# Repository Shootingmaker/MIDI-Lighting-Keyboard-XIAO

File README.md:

# MIDI-Lighting-Keyboard-XIAO  

This repository for like this video.  
  
1.[Board setting]  
File ->>> Enviroment ->>> add URL  
https://files.seeedstudio.com/arduino/package_seeeduino_boards_index.json  
 
 [Tool ->>> Setting]   
Board : Seed Studio XIAO  
USB stack : Arduino  
Debug:off  
 
2.[Library Install]  
FastLED 3.3.3 "5kft" fork.  
Tools -> Library manager.  
https://github.com/5kft/FastLED/tree/platform-xiao  
 
Arduiono MIDI 5.0  
Tools -> Library manager.  
https://github.com/FortySevenEffects/arduino_midi_library  
 
Arduino USB-MIDI  
Tools -> Library manager.  
https://github.com/lathoub/Arduino-USBMIDI  
 
MIDIUSB  
Tools -> Library manager.  
https://github.com/arduino-libraries/MIDIUSB  
 
3.[Over write "buffer memory" & "RunningStatus" setting.]  
 
 "midi_Settings.h" over write or  USE static  const  
 -> static const unsigned SysExMaxSize = 10240;  // more is better.  
 -> static const bool UseRunningStatus = true;  

4.[HARDWARE Wireing to LED (SK9822 or APA102)]  

 5V    with Capacitor 100uF is Better.  
 SDI(Serial DATA In = MOSI) is  Pin:10(XIAO)  
 CKI(Clock In)  is  Pin:8(XIAO)  
 GND

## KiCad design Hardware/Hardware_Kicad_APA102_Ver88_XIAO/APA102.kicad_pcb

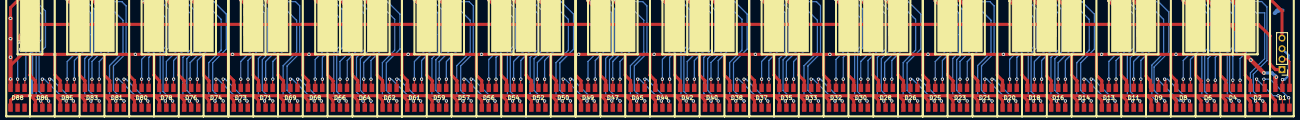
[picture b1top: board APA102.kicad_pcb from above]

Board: 2 copper layers, 89 parts (0 on the bottom side), 178 nets.

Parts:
D1, D2, D3, D4, D5, D6, D7, D8, D9, D10, D11, D12, D13, D14, D15, D16, D17, D18, D19, D20, D21, D22, D23, D24, D25, D26, D27, D28, D29, D30, D31, D32, D33, D34, D35, D36, D37, D38, D39, D40, D41, D42, D43, D44, D45, D46, D47, D48, D49, D50, D51, D52, D53, D54, D55, D56, D57, D58, D59, D60, D61, D62, D63, D64, D65, D66, D67, D68, D69, D70, D71, D72, D73, D74, D75, D76, D77, D78, D79, D80, D81, D82, D83, D84, D85, D86, D87, D88: APA102C; LED_RGB_5050-6B
J1: Conn_01x04_Female; PinHeader_1x04_P2.54mm_Vertical

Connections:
+5V: D1.1, D2.1, D3.1, D4.1, D5.1, D6.1, D7.1, D8.1, D9.1, D10.1, D11.1, D12.1, D13.1, D14.1, D15.1, D16.1, D17.1, D18.1, D19.1, D20.1, D21.1, D22.1, D23.1, D24.1, D25.1, D26.1, D27.1, D28.1, D29.1, D30.1, D31.1, D32.1, D33.1, D34.1, D35.1, D36.1, D37.1, D38.1, D39.1, D40.1, D41.1, D42.1, D43.1, D44.1, D45.1, D46.1, D47.1, D48.1, D49.1, D50.1, D51.1, D52.1, D53.1, D54.1, D55.1, D56.1, D57.1, D58.1, D59.1, D60.1, D61.1, D62.1, D63.1, D64.1, D65.1, D66.1, D67.1, D68.1, D69.1, D70.1, D71.1, D72.1, D73.1, D74.1, D75.1, D76.1, D77.1, D78.1, D79.1, D80.1, D81.1, D82.1, D83.1, D84.1, D85.1, D86.1, D87.1, D88.1, J1.1
CKO_1: D12.2, D13.5
CKO_2: D24.2, D25.5
CKO_3: D36.2, D37.5
CKO_4: D48.2, D49.5
CKO_5: D60.2, D61.5
CKO_6: D72.2, D73.5
CKO_7: D84.2, D85.5
GND: D1.6, D2.6, D3.6, D4.6, D5.6, D6.6, D7.6, D8.6, D9.6, D10.6, D11.6, D12.6, D13.6, D14.6, D15.6, D16.6, D17.6, D18.6, D19.6, D20.6, D21.6, D22.6, D23.6, D24.6, D25.6, D26.6, D27.6, D28.6, D29.6, D30.6, D31.6, D32.6, D33.6, D34.6, D35.6, D36.6, D37.6, D38.6, D39.6, D40.6, D41.6, D42.6, D43.6, D44.6, D45.6, D46.6, D47.6, D48.6, D49.6, D50.6, D51.6, D52.6, D53.6, D54.6, D55.6, D56.6, D57.6, D58.6, D59.6, D60.6, D61.6, D62.6, D63.6, D64.6, D65.6, D66.6, D67.6, D68.6, D69.6, D70.6, D71.6, D72.6, D73.6, D74.6, D75.6, D76.6, D77.6, D78.6, D79.6, D80.6, D81.6, D82.6, D83.6, D84.6, D85.6, D86.6, D87.6, D88.6, J1.4
unnamed: D1.2, D2.5
unnamed: D1.3, D2.4
unnamed: D1.4, J1.2
unnamed: D1.5, J1.3
unnamed: D2.2, D3.5
unnamed: D2.3, D3.4
unnamed: D3.2, D4.5
unnamed: D3.3, D4.4
unnamed: D4.2, D5.5
unnamed: D4.3, D5.4
unnamed: D5.2, D6.5
unnamed: D5.3, D6.4
unnamed: D6.2, D7.5
unnamed: D6.3, D7.4
unnamed: D7.2, D8.5
unnamed: D7.3, D8.4
unnamed: D8.2, D9.5
unnamed: D8.3, D9.4
unnamed: D10.2, D11.5
unnamed: D10.3, D11.4
unnamed: D9.3, D10.4
unnamed: D9.2, D10.5
unnamed: D11.2, D12.5
unnamed: D11.3, D12.4
unnamed: D13.2, D14.5
unnamed: D13.3, D14.4
unnamed: D14.2, D15.5
unnamed: D14.3, D15.4
unnamed: D15.2, D16.5
unnamed: D15.3, D16.4
unnamed: D16.2, D17.5
unnamed: D16.3, D17.4
unnamed: D17.2, D18.5
unnamed: D17.3, D18.4
unnamed: D18.2, D19.5
unnamed: D18.3, D19.4
unnamed: D19.2, D20.5
unnamed: D19.3, D20.4
unnamed: D20.2, D21.5
unnamed: D20.3, D21.4
unnamed: D21.2, D22.5
unnamed: D21.3, D22.4
unnamed: D22.2, D23.5
unnamed: D22.3, D23.4
unnamed: D23.2, D24.5
unnamed: D23.3, D24.4
unnamed: D25.2, D26.5
unnamed: D25.3, D26.4
unnamed: D26.2, D27.5
unnamed: D26.3, D27.4
unnamed: D27.2, D28.5
unnamed: D27.3, D28.4
unnamed: D28.2, D29.5
unnamed: D28.3, D29.4
unnamed: D29.2, D30.5
unnamed: D29.3, D30.4
unnamed: D30.2, D31.5
unnamed: D30.3, D31.4
unnamed: D31.2, D32.5
unnamed: D31.3, D32.4
unnamed: D32.2, D33.5
unnamed: D32.3, D33.4
unnamed: D33.2, D34.5
unnamed: D33.3, D34.4
unnamed: D34.2, D35.5
unnamed: D34.3, D35.4
unnamed: D35.2, D36.5
unnamed: D35.3, D36.4
unnamed: D37.2, D38.5
unnamed: D37.3, D38.4
unnamed: D38.2, D39.5
unnamed: D38.3, D39.4
unnamed: D39.2, D40.5
unnamed: D39.3, D40.4
unnamed: D40.2, D41.5
unnamed: D40.3, D41.4
unnamed: D41.2, D42.5
unnamed: D41.3, D42.4
unnamed: D42.2, D43.5
unnamed: D42.3, D43.4
unnamed: D43.2, D44.5
unnamed: D43.3, D44.4
unnamed: D44.2, D45.5
unnamed: D44.3, D45.4
unnamed: D45.2, D46.5
unnamed: D45.3, D46.4
unnamed: D46.2, D47.5
unnamed: D46.3, D47.4
unnamed: D47.2, D48.5
unnamed: D47.3, D48.4
unnamed: D49.2, D50.5
unnamed: D49.3, D50.4
unnamed: D50.2, D51.5
unnamed: D50.3, D51.4
unnamed: D51.2, D52.5
unnamed: D51.3, D52.4
unnamed: D52.2, D53.5
unnamed: D52.3, D53.4
unnamed: D53.2, D54.5
unnamed: D53.3, D54.4
unnamed: D54.2, D55.5
unnamed: D54.3, D55.4
unnamed: D55.2, D56.5
unnamed: D55.3, D56.4
unnamed: D56.2, D57.5
unnamed: D56.3, D57.4
unnamed: D57.2, D58.5
unnamed: D57.3, D58.4
unnamed: D58.2, D59.5
unnamed: D58.3, D59.4
unnamed: D59.2, D60.5
unnamed: D59.3, D60.4
unnamed: D61.2, D62.5
unnamed: D61.3, D62.4
unnamed: D62.2, D63.5
unnamed: D62.3, D63.4
unnamed: D63.2, D64.5
unnamed: D63.3, D64.4
unnamed: D64.2, D65.5
unnamed: D64.3, D65.4
unnamed: D65.2, D66.5
unnamed: D65.3, D66.4
unnamed: D66.2, D67.5
unnamed: D66.3, D67.4
unnamed: D67.2, D68.5
unnamed: D67.3, D68.4
unnamed: D68.2, D69.5
unnamed: D68.3, D69.4
unnamed: D69.2, D70.5
unnamed: D69.3, D70.4
unnamed: D70.2, D71.5
unnamed: D70.3, D71.4
unnamed: D71.2, D72.5
unnamed: D71.3, D72.4
unnamed: D73.2, D74.5
unnamed: D73.3, D74.4
unnamed: D74.2, D75.5
unnamed: D74.3, D75.4
unnamed: D75.2, D76.5
unnamed: D75.3, D76.4
unnamed: D76.2, D77.5
unnamed: D76.3, D77.4
unnamed: D77.2, D78.5
unnamed: D77.3, D78.4
unnamed: D78.2, D79.5
unnamed: D78.3, D79.4
unnamed: D79.2, D80.5
unnamed: D79.3, D80.4
unnamed: D80.2, D81.5
unnamed: D80.3, D81.4
unnamed: D81.2, D82.5
unnamed: D81.3, D82.4
unnamed: D82.2, D83.5
unnamed: D82.3, D83.4
unnamed: D83.2, D84.5
unnamed: D83.3, D84.4
unnamed: D85.2, D86.5
unnamed: D85.3, D86.4
unnamed: D86.2, D87.5
unnamed: D86.3, D87.4
unnamed: D87.2, D88.5
unnamed: D87.3, D88.4
SDO_1: D12.3, D13.4
SDO_2: D24.3, D25.4
SDO_3: D36.3, D37.4
SDO_4: D48.3, D49.4
SDO_5: D60.3, D61.4
SDO_6: D72.3, D73.4
SDO_7: D84.3, D85.4

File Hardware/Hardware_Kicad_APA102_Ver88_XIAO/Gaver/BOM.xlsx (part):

version | source | date | tool | number | name | tstamps | title | company | rev | date2 | source3 | number4 | value | ref | value5 | footprint | datasheet | lib | part | description | names | tstamps6 | tstamp | lib7 | part8 | description9 | docs | fp | field | name10 | num | name11 | type | logical | uri | code | name12 | ref13 | pin
D | C:\Users\shoot\Google ドライブ\Kicad\APA102\Hardware_Kicad_APA102_Ver2\APA102.sch | 2019/08/05 10:16:48 | Eeschema (5.1.0)-1 | 1 | / | / |  |  |  |  | APA102.sch | 1
D | C:\Users\shoot\Google ドライブ\Kicad\APA102\Hardware_Kicad_APA102_Ver2\APA102.sch | 2019/08/05 10:16:48 | Eeschema (5.1.0)-1 | 1 | / | / |  |  |  |  | APA102.sch | 2
D | C:\Users\shoot\Google ドライブ\Kicad\APA102\Hardware_Kicad_APA102_Ver2\APA102.sch | 2019/08/05 10:16:48 | Eeschema (5.1.0)-1 | 1 | / | / |  |  |  |  | APA102.sch | 3
D | C:\Users\shoot\Google ドライブ\Kicad\APA102\Hardware_Kicad_APA102_Ver2\APA102.sch | 2019/08/05 10:16:48 | Eeschema (5.1.0)-1 | 1 | / | / |  |  |  |  | APA102.sch | 4
D |  |  |  |  |  |  |  |  |  |  |  |  |  | D1 | APA102C | LED_SMD:LED_RGB_5050-6 | http://www.led-color.com/upload/201604/APA102-2020%20SMD%20LED.pdf | LED | APA102-2020 | RGB LED with integrated controller | / | / | 5C8DC9D1
D |  |  |  |  |  |  |  |  |  |  |  |  |  | D2 | APA102C | LED_SMD:LED_RGB_5050-6 | http://www.led-color.com/upload/201604/APA102-2020%20SMD%20LED.pdf | LED | APA102-2020 | RGB LED with integrated controller | / | / | 5C8DD250
D |  |  |  |  |  |  |  |  |  |  |  |  |  | D3 | APA102C | LED_SMD:LED_RGB_5050-6 | http://www.led-color.com/upload/201604/APA102-2020%20SMD%20LED.pdf | LED | APA102-2020 | RGB LED with integrated controller | / | / | 5C8DE2A1
D |  |  |  |  |  |  |  |  |  |  |  |  |  | D4 | APA102C | LED_SMD:LED_RGB_5050-6 | http://www.led-color.com/upload/201604/APA102-2020%20SMD%20LED.pdf | LED | APA102-2020 | RGB LED with integrated controller | / | / | 5C8DF38D
D |  |  |  |  |  |  |  |  |  |  |  |  |  | D5 | APA102C | LED_SMD:LED_RGB_5050-6 | http://www.led-color.com/upload/201604/APA102-2020%20SMD%20LED.pdf | LED | APA102-2020 | RGB LED with integrated controller | / | / | 5C8E0A32
D |  |  |  |  |  |  |  |  |  |  |  |  |  | D6 | APA102C | LED_SMD:LED_RGB_5050-6 | http://www.led-color.com/upload/201604/APA102-2020%20SMD%20LED.pdf | LED | APA102-2020 | RGB LED with integrated controller | / | / | 5C8E176C
D |  |  |  |  |  |  |  |  |  |  |  |  |  | D7 | APA102C | LED_SMD:LED_RGB_5050-6 | http://www.led-color.com/upload/201604/APA102-2020%20SMD%20LED.pdf | LED | APA102-2020 | RGB LED with integrated controller | / | / | 5C8E2378
D |  |  |  |  |  |  |  |  |  |  |  |  |  | D8 | APA102C | LED_SMD:LED_RGB_5050-6 | http://www.led-color.com/upload/201604/APA102-2020%20SMD%20LED.pdf | LED | APA102-2020 | RGB LED with integrated controller | / | / | 5C8ECEC4
D |  |  |  |  |  |  |  |  |  |  |  |  |  | D9 | APA102C | LED_SMD:LED_RGB_5050-6 | http://www.led-color.com/upload/201604/APA102-2020%20SMD%20LED.pdf | LED | APA102-2020 | RGB LED with integrated controller | / | / | 5C8ECECA
D |  |  |  |  |  |  |  |  |  |  |  |  |  | D10 | APA102C | LED_SMD:LED_RGB_5050-6 | http://www.led-color.com/upload/201604/APA102-2020%20SMD%20LED.pdf | LED | APA102-2020 | RGB LED with integrated controller | / | / | 5C8ECED0
D |  |  |  |  |  |  |  |  |  |  |  |  |  | D11 | APA102C | LED_SMD:LED_RGB_5050-6 | http://www.led-color.com/upload/201604/APA102-2020%20SMD%20LED.pdf | LED | APA102-2020 | RGB LED with integrated controller | / | / | 5C8ECED6
D |  |  |  |  |  |  |  |  |  |  |  |  |  | D12 | APA102C | LED_SMD:LED_RGB_5050-6 | http://www.led-color.com/upload/201604/APA102-2020%20SMD%20LED.pdf | LED | APA102-2020 | RGB LED with integrated controller | / | / | 5C8ECEDC
D |  |  |  |  |  |  |  |  |  |  |  |  |  | J2 | Conn_01x04_Female | JQ4:04JQST | ~ | Connector | Conn_01x04_Female | Generic connector, single row, 01x04, script generated (kicad-library-utils/sch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 | / | / | 5CA2C454
D |  |  |  |  |  |  |  |  |  |  |  |  |  | J1 | Conn_01x04_Female | Connector_JST:JST_XH_S4B-XH-A_1x04_P2.50mm_Horizontal | ~ | Connector | Conn_01x04_Female | Generic connector, single row, 01x04, script generated (kicad-library-utils/sch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 | / | / | 5CA35914
D |  |  |  |  |  |  |  |  |  |  |  |  |  |  |  |  |  |  |  |  |  |  |  | Connector | Conn_01x04_Female | Generic connector, single row, 01x04, script generated (kicad-library-utils/sch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 | ~ | Connector*:*_1x??_* | J | Reference
D |  |  |  |  |  |  |  |  |  |  |  |  |  |  |  |  |  |  |  |  |  |  |  | Connector | Conn_01x04_Female | Generic connector, single row, 01x04, script generated (kicad-library-utils/sch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 | ~ | Connector*:*_1x??_* | Conn_01x04_Female | Value
D |  |  |  |  |  |  |  |  |  |  |  |  |  |  |  |  |  |  |  |  |  |  |  | Connector | Conn_01x04_Female | Generic connector, single row, 01x04, script generated (kicad-library-utils/sch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 | ~ | Connector*:*_1x??_* |  |  | 1 | Pin_1 | passive
D |  |  |  |  |  |  |  |  |  |  |  |  |  |  |  |  |  |  |  |  |  |  |  | Connector | Conn_01x04_Female | Generic connector, single row, 01x04, script generated (kicad-library-utils/sch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 | ~ | Connector*:*_1x??_* |  |  | 2 | Pin_2 | passive
D |  |  |  |  |  |  |  |  |  |  |  |  |  |  |  |  |  |  |  |  |  |  |  | Connector | Conn_01x04_Female | Generic connector, single row, 01x04, script generated (kicad-library-utils/sch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 | ~ | Connector*:*_1x??_* |  |  | 3 | Pin_3 | passive
D |  |  |  |  |  |  |  |  |  |  |  |  |  |  |  |  |  |  |  |  |  |  |  | Connector | Conn_01x04_Female | Generic connector, single row, 01x04, script generated (kicad-library-utils/sch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 | ~ | Connector*:*_1x??_* |  |  | 4 | Pin_4 | passive
D |  |  |  |  |  |  |  |  |  |  |  |  |  |  |  |  |  |  |  |  |  |  |  | LED | APA102-2020 | RGB LED with integrated controller | http://www.led-color.com/upload/201604/APA102-2020%20SMD%20LED.pdf | LED*APA102* | D | Reference
D |  |  |  |  |  |  |  |  |  |  |  |  |  |  |  |  |  |  |  |  |  |  |  | LED | APA102-2020 | RGB LED with integrated controller | http://www.led-color.com/upload/201604/APA102-2020%20SMD%20LED.pdf | LED*APA102* | APA102-2020 | Value
D |  |  |  |  |  |  |  |  |  |  |  |  |  |  |  |  |  |  |  |  |  |  |  | LED | APA102-2020 | RGB LED with integrated controller | http://www.led-color.com/upload/201604/APA102-2020%20SMD%20LED.pdf | LED*APA102* | LED_SMD:LED-APA102-2020 | Footprint
D |  |  |  |  |  |  |  |  |  |  |  |  |  |  |  |  |  |  |  |  |  |  |  | LED | APA102-2020 | RGB LED with integrated controller | http://www.led-color.com/upload/201604/APA102-2020%20SMD%20LED.pdf | LED*APA102* |  |  | 1 | VDD | power_in
D |  |  |  |  |  |  |  |  |  |  |  |  |  |  |  |  |  |  |  |  |  |  |  | LED | APA102-2020 | RGB LED with integrated controller | http://www.led-color.com/upload/201604/APA102-2020%20SMD%20LED.pdf | LED*APA102* |  |  | 2 | CKO | output
D |  |  |  |  |  |  |  |  |  |  |  |  |  |  |  |  |  |  |  |  |  |  |  | LED | APA102-2020 | RGB LED with integrated controller | http://www.led-color.com/upload/201604/APA102-2020%20SMD%20LED.pdf | LED*APA102* |  |  | 3 | SDO | output
D |  |  |  |  |  |  |  |  |  |  |  |  |  |  |  |  |  |  |  |  |  |  |  | LED | APA102-2020 | RGB LED with integrated controller | http://www.led-color.com/upload/201604/APA102-2020%20SMD%20LED.pdf | LED*APA102* |  |  | 4 | SDI | input
D |  |  |  |  |  |  |  |  |  |  |  |  |  |  |  |  |  |  |  |  |  |  |  | LED | APA102-2020 | RGB LED with integrated controller | http://www.led-color.com/upload/201604/APA102-2020%20SMD%20LED.pdf | LED*APA102* |  |  | 5 | CKI | input
D |  |  |  |  |  |  |  |  |  |  |  |  |  |  |  |  |  |  |  |  |  |  |  | LED | APA102-2020 | RGB LED with integrated controller | http://www.led-color.com/upload/201604/APA102-2020%20SMD%20LED.pdf | LED*APA102* |  |  | 6 | GND | power_in
D |  |  |  |  |  |  |  |  |  |  |  |  |  |  |  |  |  |  |  |  |  |  |  |  |  |  |  |  |  |  |  |  |  | Connector | C:\Program Files\KiCad\share\kicad\library/Connector.lib
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
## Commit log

2020-04-23 First version.
    Transfer from teensy based.
2020-04-23 change txt
2020-04-23 add Hardware
    first comit, just copy.
    DO NOT USE THIS ver NOT WORK!!!!!!
2020-05-19 First Ver
2020-05-31 Global Brightness
    Color setting change.
    Add Global Brightness setting.
2020-05-31 add HW pic movie
    Add PCB Picture
    Add sample movie
2020-05-31 Update README.md
    change <br>
2020-05-31 Create sample.png
    pic ++
2020-05-31 Update README.md
    pic ++
2020-05-31 Update README.md
    movie ++
2020-05-31 Update README.md
    change movie url
2020-05-31 Update README.md
    change pin discription.
2020-05-31 Update README.md
    URL ++
2020-05-31 Update README.md
    pic
2020-05-31 Update README.md
    del pic
2020-05-31 Update README.md
    elaboration
2020-05-31 Create xiao_BB_wirering.jpg
    add wirering pic
2020-05-31 Update README.md
    wire pic
2020-05-31 Update README.md
    set collect pin
2020-05-31 Update README.md
    SysExMaxSize more is better.
